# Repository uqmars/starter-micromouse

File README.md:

# UQ MARS Starter Micromouse Design

This repository houses the design and drivers for the starter Micromouse design provided by UQ MARS.

To find out more about the Micromouse competition, see the rules [here](https://github.com/uqmars/micromouse-spec/releases).

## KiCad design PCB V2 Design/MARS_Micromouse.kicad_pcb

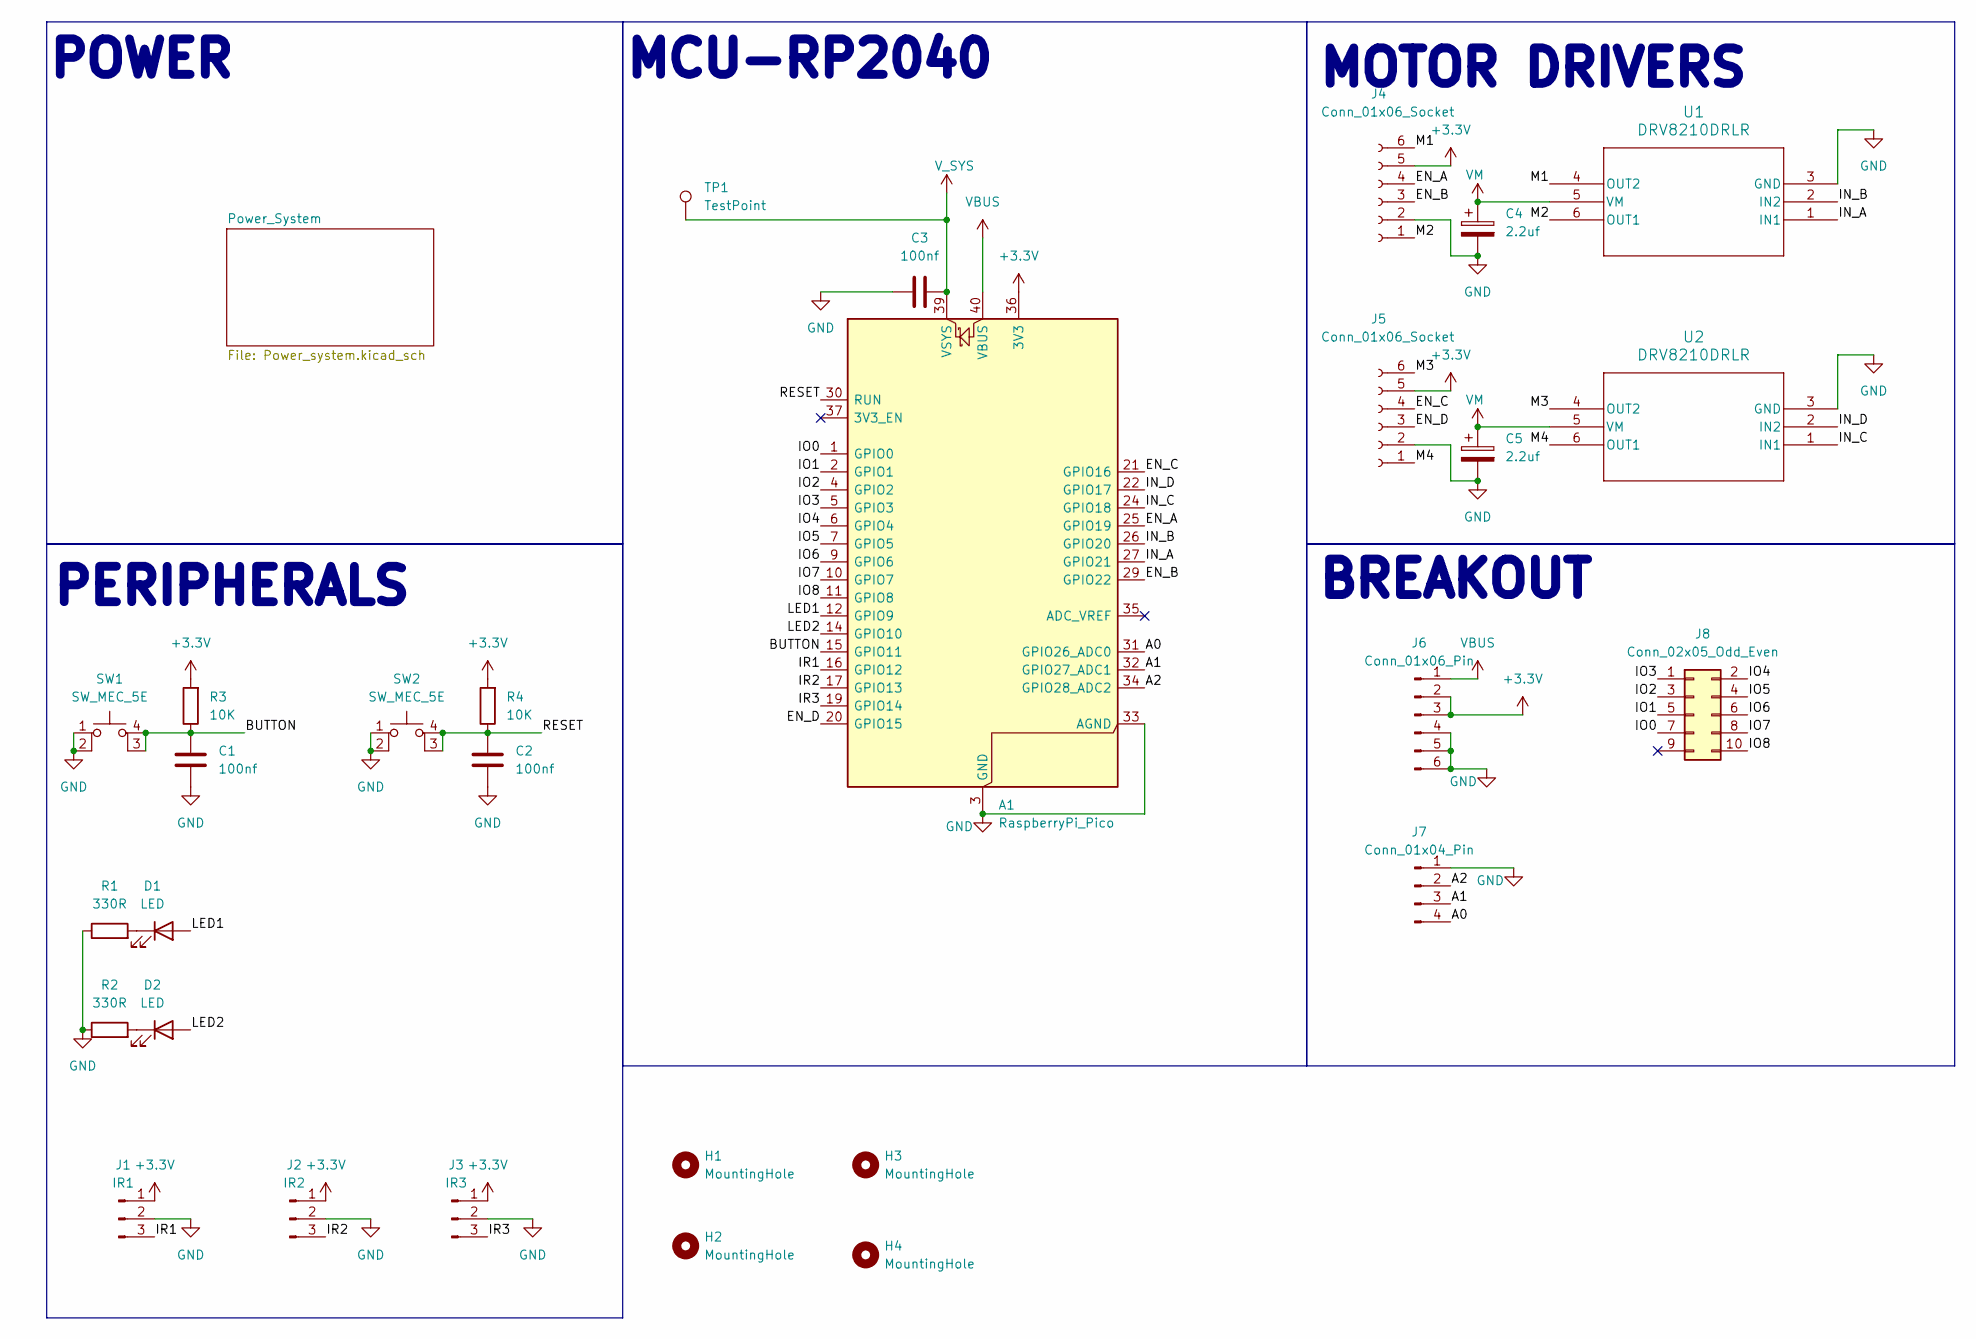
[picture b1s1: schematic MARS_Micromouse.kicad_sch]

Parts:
A1: RaspberryPi_Pico; RaspberryPi_Pico_Common_Unspecified
C1, C2, C3: 100nf; C_0603_1608Metric
C4, C5: 2.2uf; CP_Radial_D4.0mm_P2.00mm
D1, D2: LED; LED_0805_2012Metric
H1, H2, H3, H4: MountingHole; MountingHole_3.2mm_M3_ISO14580_Pad
J1: IR1; PinHeader_1x03_P2.54mm_Vertical
J2: IR2; PinHeader_1x03_P2.54mm_Vertical
J3: IR3; PinHeader_1x03_P2.54mm_Vertical
J4, J5: Conn_01x06_Socket; JST_XH_B6B-XH-A_1x06_P2.50mm_Vertical
J6: Conn_01x06_Pin; PinHeader_1x06_P2.54mm_Vertical
J7: Conn_01x04_Pin; PinHeader_1x04_P2.54mm_Vertical
J8: Conn_02x05_Odd_Even; PinHeader_2x05_P2.54mm_Vertical
R1, R2: 330R; R_0603_1608Metric
R3, R4: 10K; R_0603_1608Metric
SW1, SW2: SW_MEC_5E; SW_PUSH_6mm_H5mm
TP1: TestPoint; TestPoint_Pad_D1.0mm
U1, U2: DRV8210DRLR; SOT-563

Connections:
+3.3V: A1.36 (3V3), J1.1, J2.1, J3.1, J4.5, J5.5, J6.2, J6.3, R3.2, R4.2
/A0: A1.31 (GPIO26_ADC0), J7.4
/A1: A1.32 (GPIO27_ADC1), J7.3
/A2: A1.34 (GPIO28_ADC2), J7.2
/BUTTON: A1.15 (GPIO11), C1.1, R3.1, SW1.3 (K), SW1.4 (A)
/EN_A: A1.25 (GPIO19), J4.4
/EN_B: A1.29 (GPIO22), J4.3
/EN_C: A1.21 (GPIO16), J5.4
/EN_D: A1.20 (GPIO15), J5.3
/IN_A: A1.27 (GPIO21), U1.1 (IN1)
/IN_B: A1.26 (GPIO20), U1.2 (IN2)
/IN_C: A1.24 (GPIO18), U2.1 (IN1)
/IN_D: A1.22 (GPIO17), U2.2 (IN2)
/IO0: A1.1 (GPIO0), J8.7
/IO1: A1.2 (GPIO1), J8.5
/IO2: A1.4 (GPIO2), J8.3
/IO3: A1.5 (GPIO3), J8.1
/IO4: A1.6 (GPIO4), J8.2
/IO5: A1.7 (GPIO5), J8.4
/IO6: A1.9 (GPIO6), J8.6
/IO7: A1.10 (GPIO7), J8.8
/IO8: A1.11 (GPIO8), J8.10
/IR1: A1.16 (GPIO12), J1.3
/IR2: A1.17 (GPIO13), J2.3
/IR3: A1.19 (GPIO14), J3.3
/LED1: A1.12 (GPIO9), D1.2 (A)
/LED2: A1.14 (GPIO10), D2.2 (A)
/M1: J4.6, U1.4 (OUT2)
/M2: J4.1, U1.6 (OUT1)
/M3: J5.6, U2.4 (OUT2)
/M4: J5.1, U2.6 (OUT1)
/RESET: A1.30 (RUN), C2.1, R4.1, SW2.3 (K), SW2.4 (A)
GND: A1.3 (GND), A1.8 (GND), A1.13 (GND), A1.18 (GND), A1.23 (GND), A1.28 (GND), A1.33 (AGND), A1.38 (GND), C1.2, C2.2, C3.1, C4.2, C5.2, J1.2, J2.2, J3.2, J4.2, J5.2, J6.4, J6.5, J6.6, J7.1, R1.1, R2.1, SW1.1, SW1.2, SW2.1, SW2.2, U1.3 (GND), U2.3 (GND); also elsewhere on the board
unnamed: D1.1 (K), R1.2
unnamed: D2.1 (K), R2.2
VBUS: A1.40 (VBUS), J6.1; also elsewhere on the board
VM: C4.1, C5.1, U1.5 (VM), U2.5 (VM); also elsewhere on the board
V_SYS: A1.39 (VSYS), C3.2, TP1.1 (1_1); also elsewhere on the board

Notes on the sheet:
POWER
MCU-RP2040
BREAKOUT
MOTOR DRIVERS
PERIPHERALS

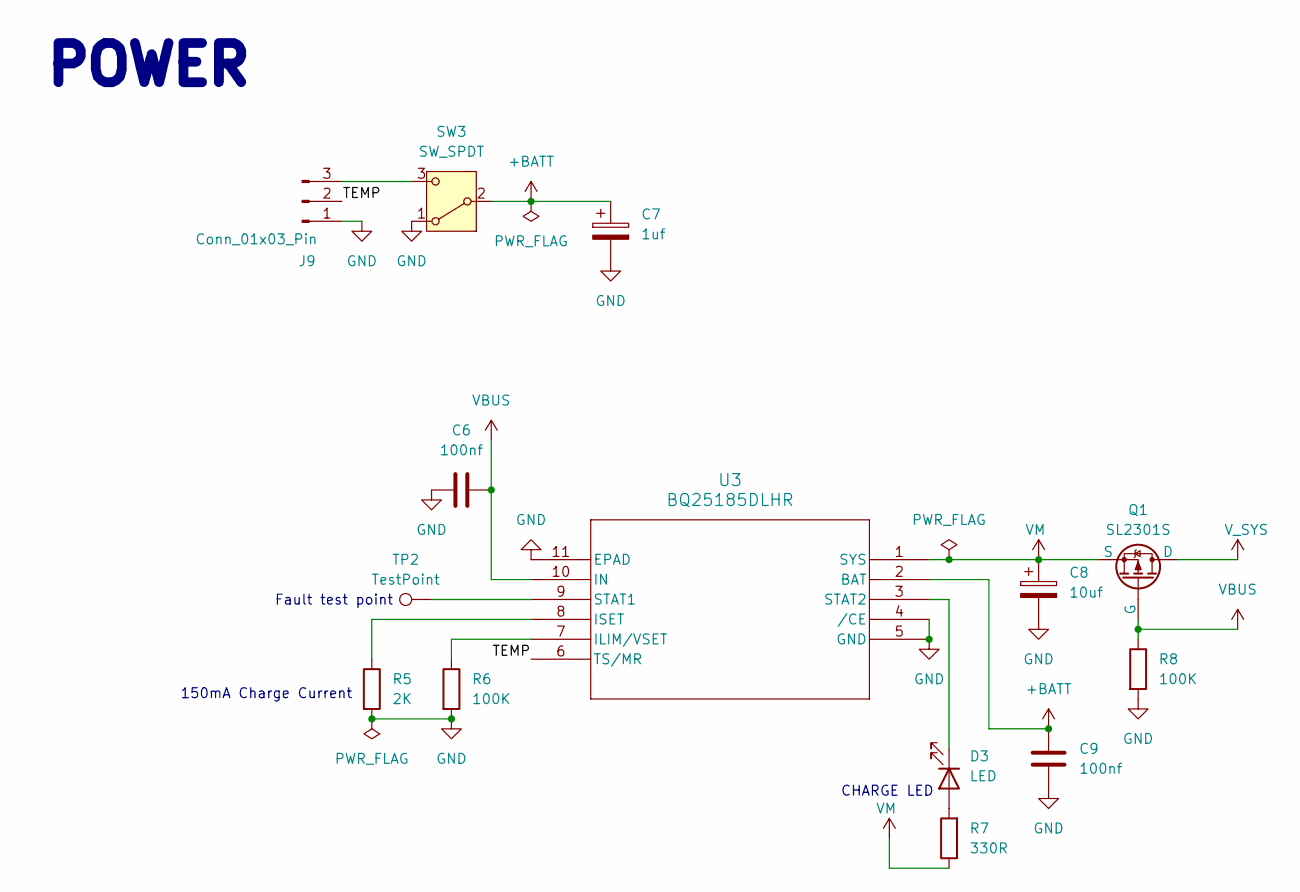
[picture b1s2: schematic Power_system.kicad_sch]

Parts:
C6, C9: 100nf; C_0603_1608Metric
C7: 1uf; CP_Radial_D4.0mm_P2.00mm
C8: 10uf; CP_Radial_D5.0mm_P2.50mm
D3: LED; LED_0805_2012Metric
J9: Conn_01x03_Pin; JST_PH_B3B-PH-K_1x03_P2.00mm_Vertical
Q1: SL2301S; SOT-23
R5: 2K; R_0603_1608Metric
R6, R8: 100K; R_0603_1608Metric
R7: 330R; R_0603_1608Metric
SW3: SW_SPDT; SLW-1678105-6A-N-D
TP2: TestPoint; TestPoint_Pad_D1.0mm
U3: BQ25185DLHR; WSON10_DLH_TEX

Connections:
+BATT: C7.1, C9.2, SW3.2 (B), U3.2 (BAT)
/Power_System/TEMP: J9.2, U3.6 (TS/MR)
GND: C6.2, C7.2, C8.2, C9.1, J9.1, R5.2, R6.2, R8.2, SW3.1 (A), U3.4 (/CE), U3.5 (GND), U3.11 (EPAD); also elsewhere on the board
unnamed: D3.2 (A), R7.2
unnamed: D3.1 (K), U3.3 (STAT2)
unnamed: J9.3, SW3.3 (C)
unnamed: R6.1, U3.7 (ILIM/VSET)
unnamed: R5.1, U3.8 (ISET)
unnamed: TP2.1 (1_1), U3.9 (STAT1)
VBUS: C6.1, Q1.2 (G), R8.1, U3.10 (IN); also elsewhere on the board
VM: C8.1, Q1.3 (S), R7.1, U3.1 (SYS); also elsewhere on the board
V_SYS: Q1.1 (D); also elsewhere on the board

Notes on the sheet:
Fault test point
POWER
CHARGE LED
150mA Charge Current

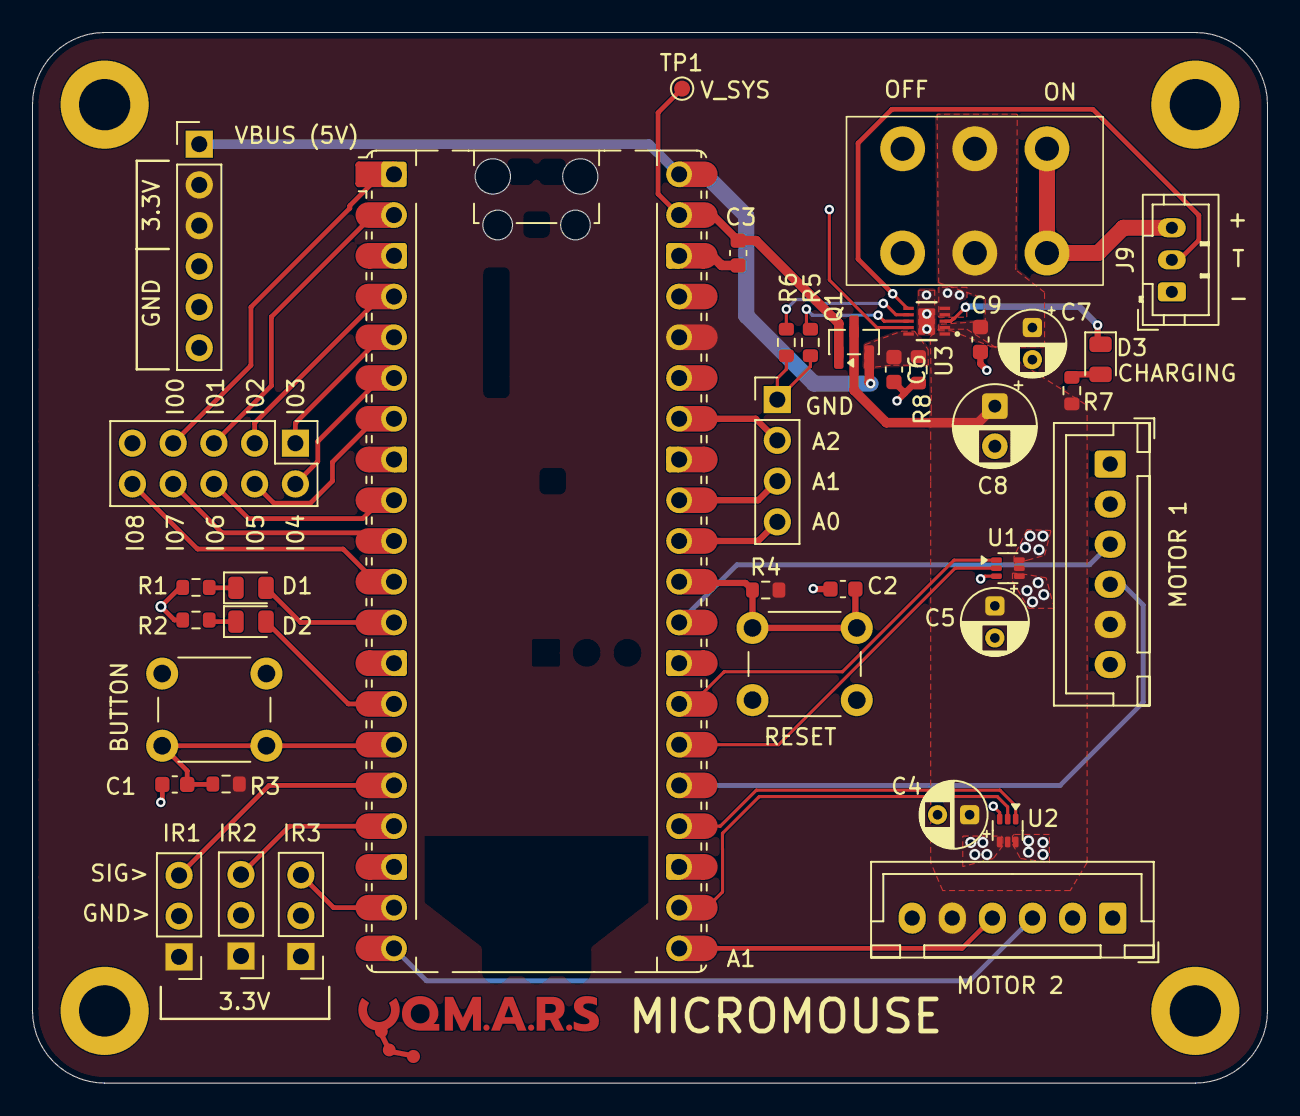
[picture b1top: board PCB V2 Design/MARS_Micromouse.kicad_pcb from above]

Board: 2 copper layers, 77.0 x 65.5 mm, 43 parts (1 on the bottom side), 46 nets.

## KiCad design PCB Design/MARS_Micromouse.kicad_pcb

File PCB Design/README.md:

# MARS_Micromouse
Micromouse pcb designed for the UQ MARS micromouse workshop series.

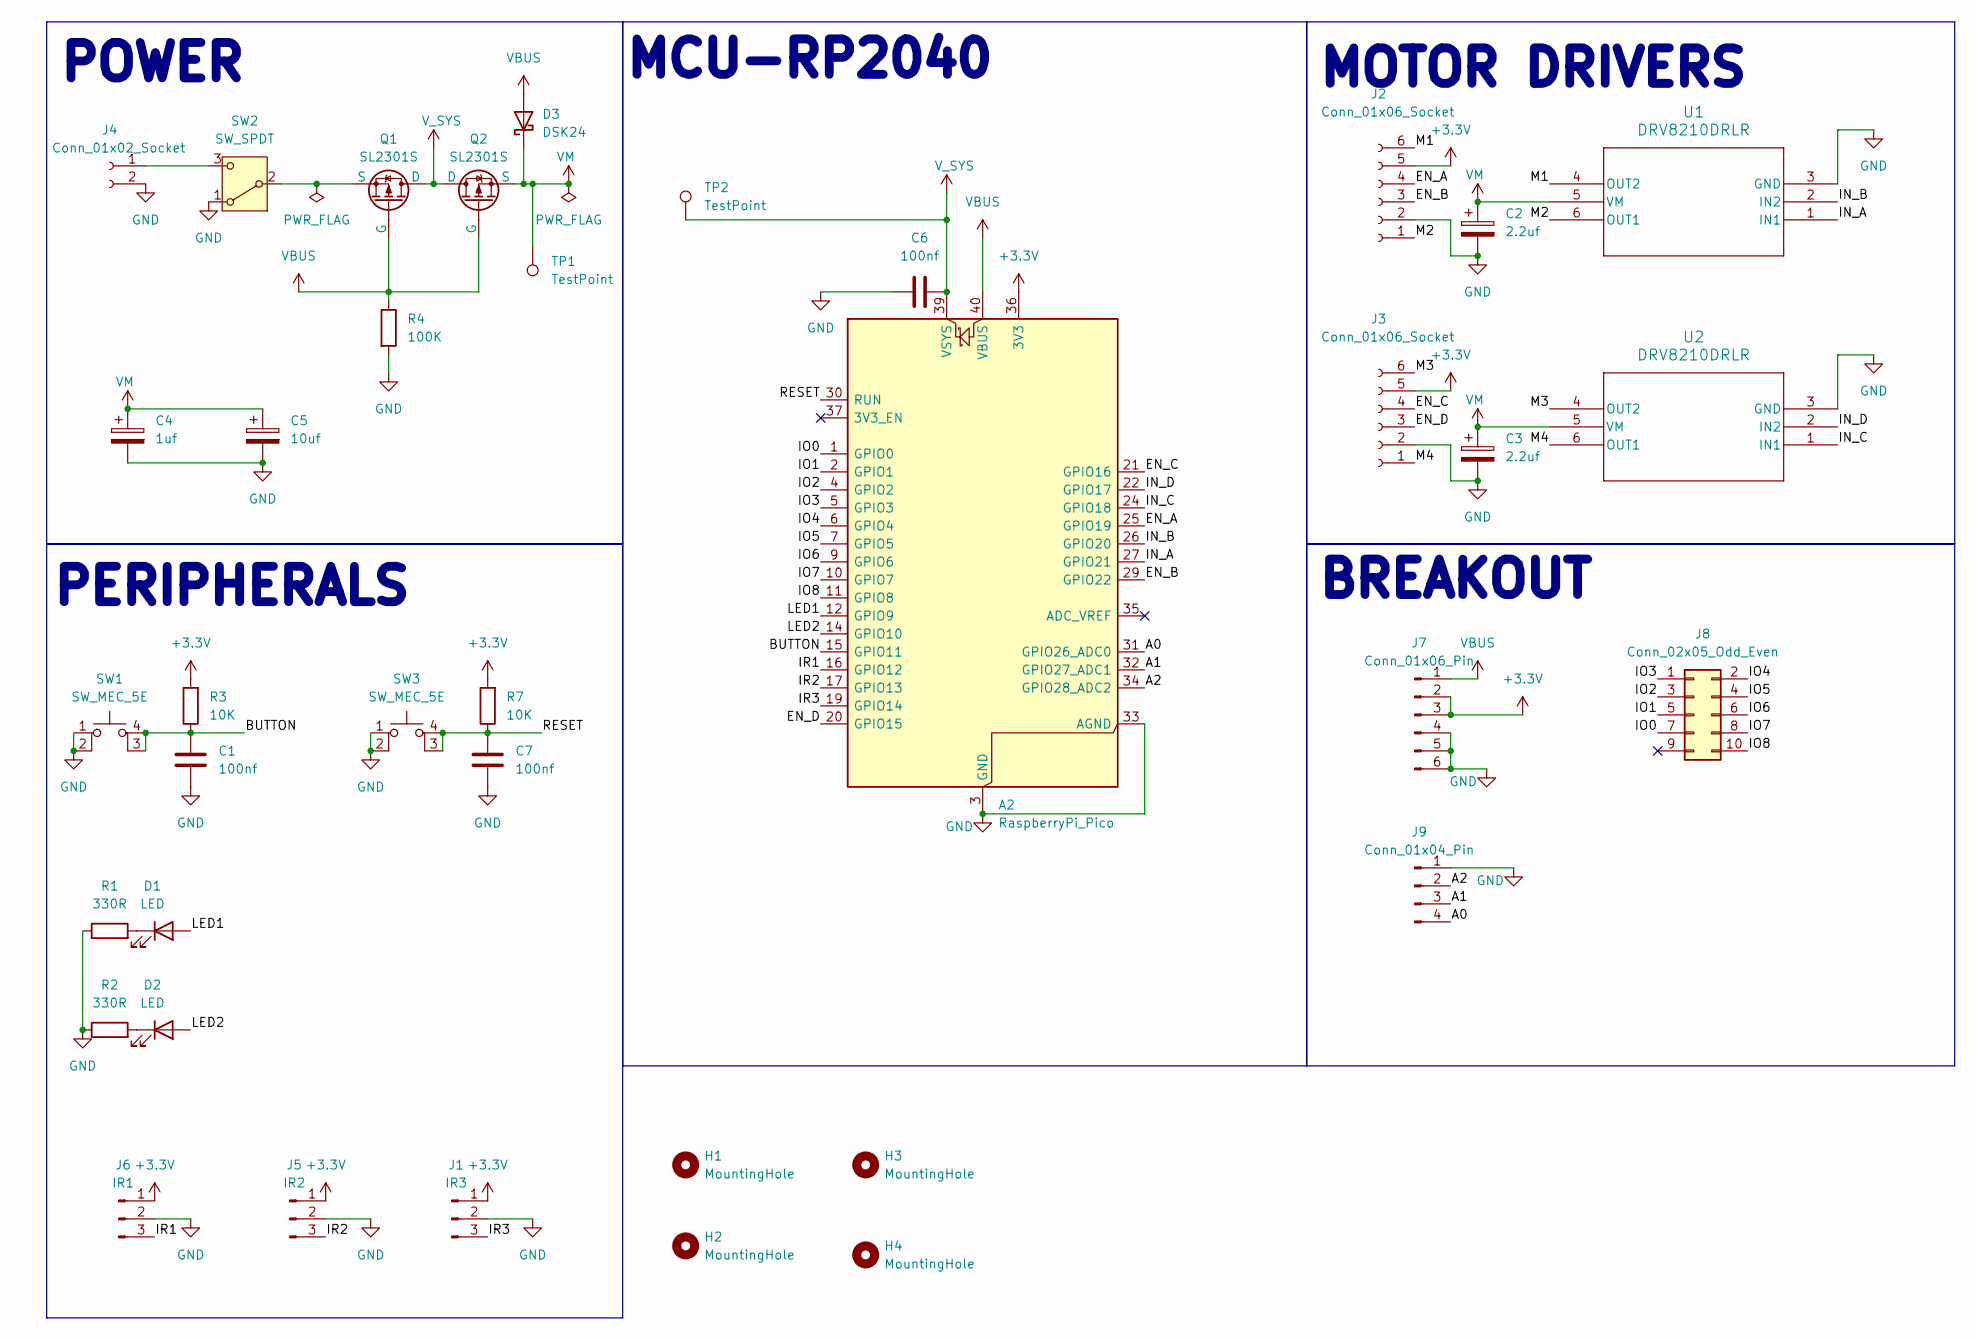
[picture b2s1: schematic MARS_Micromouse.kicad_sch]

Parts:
A2: RaspberryPi_Pico; RaspberryPi_Pico_Common_Unspecified
C1, C6, C7: 100nf; C_0603_1608Metric
C2, C3: 2.2uf; CP_Radial_D4.0mm_P2.00mm
C4: 1uf; CP_Radial_D4.0mm_P2.00mm
C5: 10uf; CP_Radial_D5.0mm_P2.50mm
D1, D2: LED; LED_0805_2012Metric
D3: DSK24; D_SOD-123F
H1, H2, H3, H4: MountingHole; MountingHole_3.2mm_M3_ISO14580_Pad
J1: IR3; PinHeader_1x03_P2.54mm_Vertical
J2, J3: Conn_01x06_Socket; JST_XH_B6B-XH-A_1x06_P2.50mm_Vertical
J4: Conn_01x02_Socket; JST_XH_B2B-XH-A_1x02_P2.50mm_Vertical
J5: IR2; PinHeader_1x03_P2.54mm_Vertical
J6: IR1; PinHeader_1x03_P2.54mm_Vertical
J7: Conn_01x06_Pin; PinHeader_1x06_P2.54mm_Vertical
J8: Conn_02x05_Odd_Even; PinHeader_2x05_P2.54mm_Vertical
J9: Conn_01x04_Pin; PinHeader_1x04_P2.54mm_Vertical
Q1, Q2: SL2301S; SOT-23
R1, R2: 330R; R_0603_1608Metric
R3, R7: 10K; R_0603_1608Metric
R4: 100K; R_0603_1608Metric
SW1, SW3: SW_MEC_5E; SW_PUSH_6mm_H5mm
SW2: SW_SPDT; SLW-1678105-6A-N-D
TP1, TP2: TestPoint; TestPoint_Pad_D1.0mm
U1, U2: DRV8210DRLR; SOT-563

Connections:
+3.3V: A2.36 (3V3), J1.1, J2.5, J3.5, J5.1, J6.1, J7.2, J7.3, R3.2, R7.2
/A0: A2.31 (GPIO26_ADC0), J9.4
/A1: A2.32 (GPIO27_ADC1), J9.3
/A2: A2.34 (GPIO28_ADC2), J9.2
/BUTTON: A2.15 (GPIO11), C1.1, R3.1, SW1.3 (K), SW1.4 (A)
/EN_A: A2.25 (GPIO19), J2.4
/EN_B: A2.29 (GPIO22), J2.3
/EN_C: A2.21 (GPIO16), J3.4
/EN_D: A2.20 (GPIO15), J3.3
/IN_A: A2.27 (GPIO21), U1.1 (IN1)
/IN_B: A2.26 (GPIO20), U1.2 (IN2)
/IN_C: A2.24 (GPIO18), U2.1 (IN1)
/IN_D: A2.22 (GPIO17), U2.2 (IN2)
/IO0: A2.1 (GPIO0), J8.7
/IO1: A2.2 (GPIO1), J8.5
/IO2: A2.4 (GPIO2), J8.3
/IO3: A2.5 (GPIO3), J8.1
/IO4: A2.6 (GPIO4), J8.2
/IO5: A2.7 (GPIO5), J8.4
/IO6: A2.9 (GPIO6), J8.6
/IO7: A2.10 (GPIO7), J8.8
/IO8: A2.11 (GPIO8), J8.10
/IR1: A2.16 (GPIO12), J6.3
/IR2: A2.17 (GPIO13), J5.3
/IR3: A2.19 (GPIO14), J1.3
/LED1: A2.12 (GPIO9), D1.2 (A)
/LED2: A2.14 (GPIO10), D2.2 (A)
/M1: J2.6, U1.4 (OUT2)
/M2: J2.1, U1.6 (OUT1)
/M3: J3.6, U2.4 (OUT2)
/M4: J3.1, U2.6 (OUT1)
/RESET: A2.30 (RUN), C7.1, R7.1, SW3.3 (K), SW3.4 (A)
GND: A2.3 (GND), A2.8 (GND), A2.13 (GND), A2.18 (GND), A2.23 (GND), A2.28 (GND), A2.33 (AGND), A2.38 (GND), C1.2, C2.2, C3.2, C4.2, C5.2, C6.1, C7.2, J1.2, J2.2, J3.2, J4.2, J5.2, J6.2, J7.4, J7.5, J7.6, J9.1, R1.1, R2.1, R4.2, SW1.1, SW1.2, SW2.1 (A), SW3.1, SW3.2, U1.3 (GND), U2.3 (GND)
unnamed: D1.1 (K), R1.2
unnamed: D2.1 (K), R2.2
unnamed: J4.1, SW2.3 (C)
unnamed: Q1.3 (S), SW2.2 (B)
VBUS: A2.40 (VBUS), D3.2 (A), J7.1, Q1.2 (G), Q2.2 (G), R4.1
VM: C2.1, C3.1, C4.1, C5.1, D3.1 (K), Q2.3 (S), TP1.1, U1.5 (VM), U2.5 (VM)
V_SYS: A2.39 (VSYS), C6.2, Q1.1 (D), Q2.1 (D), TP2.1

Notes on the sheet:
MCU-RP2040
BREAKOUT
MOTOR DRIVERS
PERIPHERALS
POWER

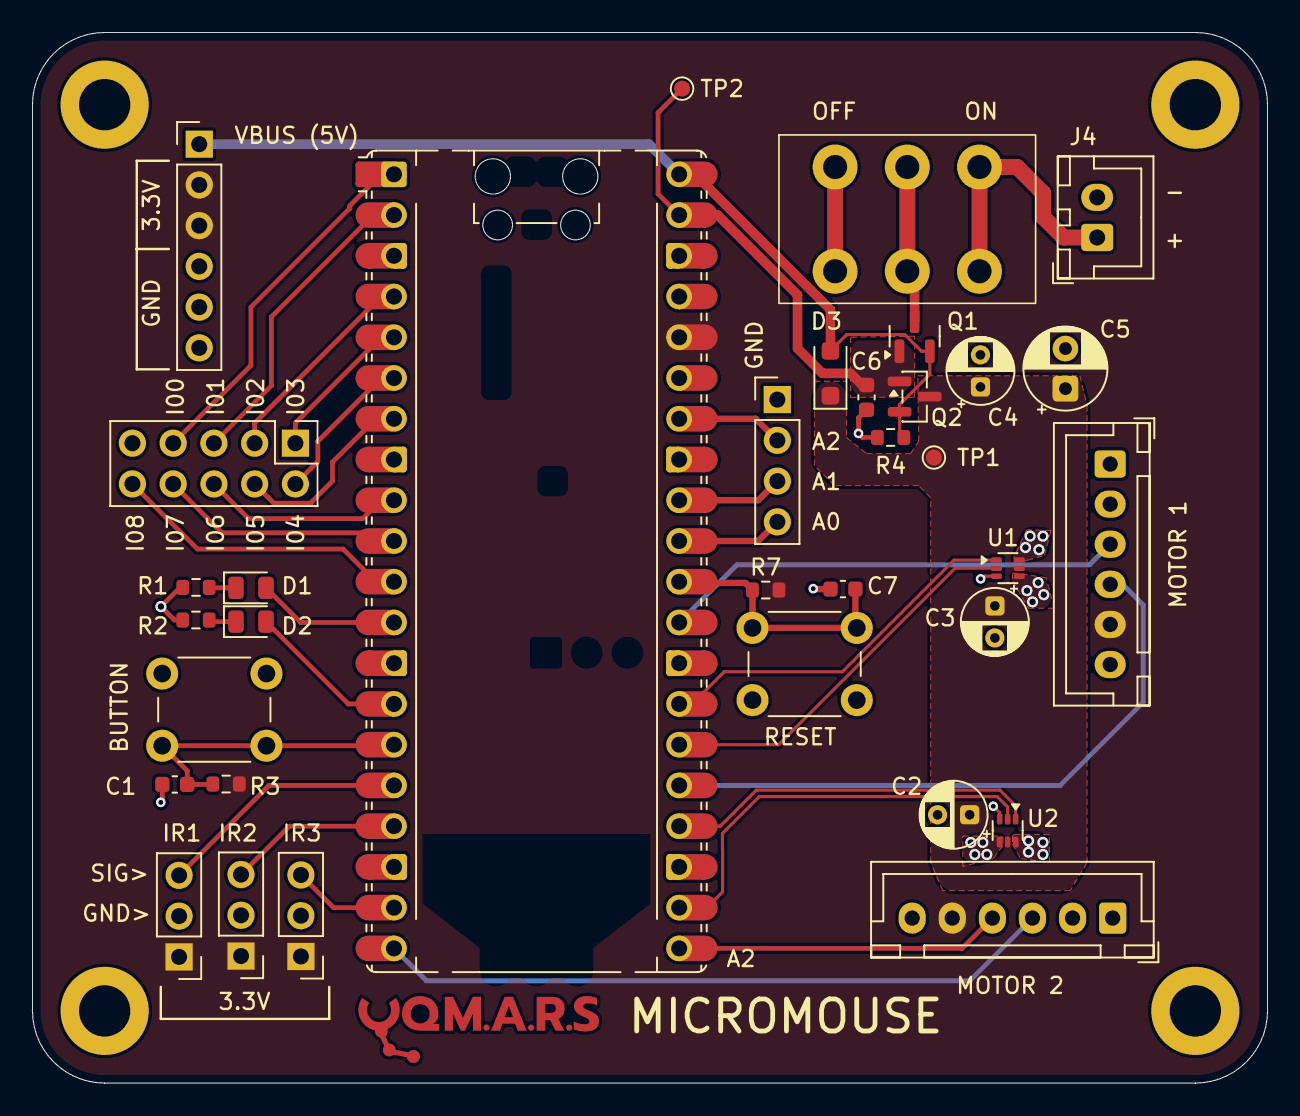
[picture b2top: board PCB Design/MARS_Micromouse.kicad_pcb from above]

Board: 2 copper layers, 77.0 x 65.5 mm, 38 parts (0 on the bottom side), 40 nets.

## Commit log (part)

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2025-12-20 Implemented a basic structure for the device drivers with basic LED control.
2025-12-29 Added further LED, IR, and motor pinouts, and added basic motor driving code.
2026-01-03 Further refined the documentation and added further object methods for ease of use.
2026-01-03 Added IR Object Sensor functionality, and added some response to the base main implementation.
2026-01-04 Framework made
2026-01-04 Updates complete
    - Added pwm control to the motors
    - Added various helper functions to read various sensors
    - Renamed IR and motor scheme to make it consistent with the PCB markings
2026-01-06 Changed master file name
2026-01-06 PCB Files, CAD, and draft BOM document added
